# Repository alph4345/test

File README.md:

# Supercapacitor-powered gadgets

Small games, e-ink displays, blinky jewellery and music toys that charge from
USB-C in minutes and run from a **supercapacitor instead of a LiPo**. The
idea comes from the
[rechargeable supercapacitor Fibonacci earrings](https://lectronz.com/products/rechargeable-supercapacitor-fibonacci-earrings-2).

This repository has:

* **[TrinketCore](hardware/trinketcore)**: an all-in-one 40 × 60 mm trinket
  board with PCBWay order files. It has:
  * pads for two capacitors lying flat on the back;
  * USB-C charging with red "charging" and green "full" LEDs;
  * an RP2040 with 16 MB of flash;
  * a socket for OLED or colour TFT modules (the board reads its charge
    level and can show it);
  * a speaker amplifier, buttons, a wake-up clock and an expansion header.
* **[CapCore](hardware/capcore)**: an open, ready-to-order 21 × 48 mm power
  module (KiCad 7). It has a USB-C charger, capacitor protection, a power
  button, a wake-up clock and a 3.3 V output for your microcontroller.
  Gerbers and JLCPCB assembly files are included.
* **[The burst method](docs/trinket-design-method.md)**: how music boxes,
  games, pets and charms last days to weeks on a capacitor, and how colour
  TFT screens fit in.
* **[Energy budget](docs/energy-budget.md)**: how long a capacitor actually
  runs each kind of gadget, plus a [calculator](tools/energy_calc.py).
* **[Choosing a capacitor](docs/choosing-a-capacitor.md)**: lithium-ion
  capacitors vs. ordinary supercapacitors, part numbers, safety rules.
* **[Buy or build?](docs/buy-or-build.md)**: sourcing options and costs.
* **[n0va Books](bookkeeping)**: the bookkeeping app for n0va crafts & creations.
  Customer profiles, branded estimates, invoices and receipts, payments taken
  through Square, sales tax profiles, expenses with receipt photos, a mileage log
  and a tax-time summary. Open `bookkeeping/index.html` in a browser; nothing to install.
* **[Firmware examples](firmware)**: Arduino and MicroPython code for power
  button, sleep/wake, capacitor gauge and shutdown on CapCore, and
  CircuitPython charge-gauge, music-box and e-ink tarot-oracle examples for TrinketCore.

| TrinketCore top | TrinketCore back | CapCore top | CapCore bottom |
|---|---|---|---|
|  |  |  |  |

## The short answer

* **Capacitors are safe and fast but small.** A 3.8 V lithium-ion capacitor
  (LIC) the size of your fingertip stores ~30 mWh, about a tenth of a
  tiny 100 mAh LiPo. The largest common one (16 × 25 mm) stores ~210 mWh. In
  exchange it charges in minutes, lasts tens of thousands of cycles, and is
  far less of a fire risk. Plain 2.7 V supercapacitors (EDLCs) are essentially
  inert but hold about a tenth as much again for the same size.
* **What that runs, per charge** (with a 120 F LIC, 12.5 × 25 mm):
  LED jewellery ~1.5 days · e-ink display updated hourly ~6 weeks ·
  OLED handheld game ~50 min · MP3 player on a speaker ~15 min.
  E-ink and jewellery are great fits, games work for short sessions, music
  players are a stretch. [Details](docs/energy-budget.md).
* **The electronics matter.** LICs must never go below 2.2 V or above 3.8 V,
  and LiPo chargers (4.2 V) would destroy them. CapCore handles that: it
  charges to 3.71 V, disconnects at 2.61 V and stays off until USB returns.
  Build it for ordinary supercapacitors instead by changing two resistors.

## Quick start

1. Pick a capacitor: [choosing a capacitor](docs/choosing-a-capacitor.md).
2. **For a complete trinket:** order TrinketCore assembled from PCBWay with the
   files in [`hardware/trinketcore/fab`](hardware/trinketcore/fab). See
   [ordering](hardware/trinketcore/README.md#ordering-from-pcbway). Plug in a
   display module, fit the capacitors, and load the
   [CircuitPython examples](firmware/trinketcore).
3. **For your own microcontroller board:** order CapCore from JLCPCB with the
   files in [`hardware/capcore/fab`](hardware/capcore/fab) (see
   [ordering](hardware/capcore/README.md#ordering-from-jlcpcb)), run the
   [bring-up checks](hardware/capcore/README.md#bring-up), and wire it to your
   microcontroller ([Pico, Feather, bare chips](hardware/capcore/README.md#connecting-a-microcontroller)).

## Status

Both designs are complete and machine-checked: each schematic and PCB matches
its netlist pin for pin, and KiCad DRC is clean apart from cosmetic footprint
warnings. **Neither board has been manufactured and tested yet.** Order a
small first batch and follow the bring-up steps before building anything you
depend on.

## Repository layout

```
bookkeeping/            n0va Books: customers, invoices, payments, expenses, taxes
docs/                   guides and board renders
firmware/               Arduino + MicroPython (CapCore), CircuitPython (TrinketCore)
hardware/trinketcore/   all-in-one board: KiCad project, PCBWay files, generator scripts
hardware/capcore/       power module: KiCad project, JLCPCB files, generator scripts
tools/energy_calc.py    runtime calculator
```

No license file yet. Pick one before sharing the design: for example
CERN-OHL-P-2.0 for the hardware and MIT for the code.

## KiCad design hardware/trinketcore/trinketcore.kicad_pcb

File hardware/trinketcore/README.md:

# TrinketCore: the all-in-one supercapacitor trinket board

TrinketCore puts everything a small rechargeable gadget needs on one
40 × 60 mm board, ready to order assembled from PCBWay:

* **Room for two capacitors.** They lie flat on the back, wired in parallel.
* **USB-C charging**, with a **red "charging" and a green "full" LED**.
* **A socket for an OLED or colour TFT module.** The microcontroller reads
  the capacitor's charge and can show it on the screen.
* **An RP2040 microcontroller** with 16 MB of flash for code, sounds and
  pictures.
* **A speaker amplifier**, two buttons, a user LED, a wake-up clock and an
  expansion header for LEDs, buttons and a lid switch.

The power side is [CapCore](../capcore)'s proven circuit. It cuts off before
the capacitor over-discharges, uses a soft power switch that turns the whole
board off, and has a buck-boost converter that keeps 3.3 V steady as the
capacitor drains.

| Top | Bottom (capacitor bay) |
|---|---|
|  |  |

*Renders of the actual Gerber layers. The display plugs into the socket along
the top edge. The capacitors solder into the pads on the left and lie flat
inside the outlines on the back.*

## What's on the board

| | |
|---|---|
| Capacitors | BT1 + BT2 in parallel: one or two 3.8 V lithium-ion capacitors (LIC). **EDLC build:** 2.7 V supercapacitors |
| Charging | USB-C, TI BQ25173, 300 mA: two 220 F capacitors fill in about 30 minutes. **Red LED (CHG)** while charging, **green LED (FULL)** when full (USB plugged in) |
| Protection | disconnects at **2.61 V** (LIC) / **1.96 V** (EDLC) and stays off until USB returns; ship mode for storage |
| Power switch | the whole board is **off between uses (about 5 µA)**. It turns on from button A, a lid/tilt switch on `WAKE`, the clock alarm, or USB. Firmware keeps it on with `HOLD` |
| 3.3 V | TI TPS63031 buck-boost, ~500 mA even from a nearly empty capacitor |
| Microcontroller | Raspberry Pi RP2040, 12 MHz crystal, **16 MB** Winbond flash, USB-C data for programming, BOOT and RESET buttons (SWD is not broken out: the USB bootloader is in ROM) |
| Display | **J4**: socket for SPI TFT/OLED modules (GND VCC SCL SDA RES DC CS BLK), backlight dimmable by PWM. **J5**: 4-pin I²C OLED socket. **J8**: Qwiic/STEMMA QT |
| Charge reading | capacitor voltage on an ADC pin, plus "charging" and "USB present" inputs |
| Sound | MAX98357A I²S class-D amplifier, 9 dB gain, shut down when idle; **J7** speaker connector (JST PH 2.0 or solder the wires) |
| Clock | NXP PCF8563 real-time clock: wakes the board on a timer or alarm (virtual pets, e-ink updates) |
| Buttons | **A / POWER** (turns the board on and is readable by firmware), **B**, BOOT, RESET |
| LEDs | red CHG, green FULL (charging), blue user LED on GP25 |
| Expansion | **J6**, 14 pins: GP0–GP7, GP28–GP29 (analog), `WAKE`, `VSYS`, 3V3, GND |
| Board | 4 layers, 40 × 60 × 1.6 mm, all parts on top, PCBWay standard rules (6/6 mil, 0.3 mm holes) |

## Which display?

The socket fits the common 0.96–1.54″ modules, so you can try several and pick
per product. A screen is the second-biggest power draw after a speaker, so
the firmware uses it in short bursts: wake, show, dim, switch off.

| Display | Colour | Draw (with the RP2040 running) | Good for |
|---|---|---|---|
| 0.96″ SSD1306 OLED, 128 × 64 (SPI on J4 or I²C on J5) | mono | ~35–40 mA; dark screens use less | games, menus, pets |
| 1.3–1.54″ ST7789 IPS TFT, 240 × 240 | **full colour** | ~45 mA at 60 % backlight, ~30 mA dimmed | colour animations, charms, games |
| 1.28″ GC9A01 round TFT, 240 × 240 | **full colour** | about the same as the ST7789 | keychain "digital charms" |
| 1.54″ 200 × 200 or 3.7″ 480 × 280 e-paper module (SSD1681 and similar) | black/white, 4 greys, or black/white/red | nothing between refreshes; ~30 mA for 2–3 s per black/white refresh (~14 s for three-colour) | tarot oracles, badges, pets, clocks: always visible |

**Yes, colour TFTs work well.** The backlight is most of the extra power, so
dim it and switch off after a few seconds. On two 220 F capacitors a colour
charm shown for 10 s, 30 times a day, lasts about four weeks. Played
continuously, a colour game lasts about two hours. See
[the design method](../../docs/trinket-design-method.md) for the numbers.

Module pin orders vary. Modules labelled `GND VCC SCL SDA RES DC CS BLK` plug
straight into J4. Seven-pin OLEDs (`GND VCC D0 D1 RES DC CS`) use the first
seven positions. Others, including many GC9A01 modules (`VCC GND ...`), need
short jumper wires. **Check that GND and VCC line up before plugging in.**

**E-ink works too**, and suits anything that should stay visible: the image
costs no power at all once drawn, so the board can switch fully off. E-paper
modules have a BUSY output where TFTs have a backlight input. Wire them to J4
by function (VCC → 3V3, GND, DIN → MOSI, CLK → SCK, CS, DC, RST → RES) with
BUSY on the BLK pin, which the RP2040 reads on GP13. The
[oracle example](../../firmware/trinketcore/circuitpython/oracle/code.py) shows a
random tarot card this way.

## Runtime per charge

LIC build, 85 % converter efficiency, 5 µA standby
([`tools/energy_calc.py`](../../tools/energy_calc.py)):

| Trinket | 1 × 120 F | 1 × 220 F | 2 × 220 F |
|---|---|---|---|
| Music box: 20 s tune + LEDs (~70 mA), 10 plays a day | 75 plays (8 days) | 138 plays (14 days) | 276 plays (4 weeks) |
| Colour TFT charm: 10 s shows (45 mA), 30 a day | 8 days | 14 days | 4 weeks |
| Virtual pet on e-paper: wakes every 30 min (30 mA × 3 s) | 3 weeks | 6 weeks | 3 months* |
| Tarot oracle on e-paper: a card per press (30 mA × 5 s), 10 a day | 600 draws (2 months) | 1,100 draws* | 2,200 draws* |
| OLED game, continuous (40 mA) | 45 min | 80 min | 2.7 h |
| Colour TFT game, continuous (55 mA) | 33 min | 60 min | 2 h |

\* Beyond a month or two the capacitors' own self-discharge dominates.

## Fitting the capacitors

The two capacitor positions sit along the left edge. **Square pad = +.** Each
position takes a 5.0 mm lead pitch (10–12.5 mm cans) or 3.5 mm (8 mm cans).
Bend 16 mm cans' 7.5 mm leads in slightly. Bend the leads 90° so each can lies
flat on the back inside its outline (`CAP 1`, `CAP 2`), with its leads at the
left edge. Stick a strip of Kapton tape under each can, and glue or strap
large cans.

* One capacitor is fine: fit either position.
* Two capacitors must be **the same type** (both LIC, or both EDLC on an EDLC
  build). Sizes may differ.
* Good choices: Eaton HS1225-3R8127-R (120 F, 12.5 × 25 mm) or HS1625-3R8227-R
  (220 F, 16 × 25 mm). See [choosing a capacitor](../../docs/choosing-a-capacitor.md).

> **Never fit a 2.7 V supercapacitor to a board built with the LIC values.**
> It would be charged to 3.71 V and can vent. Tick the build box on the back,
> and measure the charge voltage before fitting capacitors (see
> [Bring-up](#bring-up)).

## Pinout

**J4 display socket** (top edge, pin 1 = square pad, left):
GND · 3V3 · SCK (GP10) · MOSI (GP11) · RES (GP12) · DC (GP9) · CS (GP8) · BLK (GP13 via 100 Ω)

**J5 I²C OLED socket**: GND · 3V3 · SCL (GP17) · SDA (GP16).
**J8 Qwiic**: GND · 3V3 · SDA · SCL. The same bus as the clock (address 0x51),
with 4.7 kΩ pull-ups.

**J6 expansion** (right edge, pin 1 at the top): GP7 · GP6 · GP5 · GP4 · GP3 ·
GP2 · GP1 · GP0 · GP29 · GP28 · WAKE · VSYS · 3V3 · GND. The order matches the
RP2040's pins, which keeps the tracks from crossing; the back silkscreen labels
every pin.

* `WAKE`: pull to GND to switch the board on (lid, tilt, reed or vibration
  switch). For a **lid** that may stay open, put a 1 µF capacitor in series
  with the switch and a 22 MΩ resistor across that capacitor. Opening the
  lid then sends one wake pulse, and the board can still switch itself off.
* `VSYS`: the capacitor voltage (2.6–3.7 V), on only while the board runs.
  Use it for vibration motors or LED strips that tolerate it.
* GPIO pins drive LEDs directly, up to ~8 mA each through a resistor.

**J7 speaker**: 8 Ω, 0.5–1 W. **GPIO map**: see the
[firmware README](../../firmware/trinketcore/README.md#pin-map).

## LEDs and power states

| LED | Meaning |
|---|---|
| red **CHG** | charging |
| green **FULL** | USB plugged in and the capacitors are full |
| red and green blinking alternately | charger fault (for example a capacitor wired backwards, or overheating) |
| blue | yours (GP25) |

With USB plugged in the board also switches on, so a gauge can show charging
progress. Cut jumper **JP1** on the back if plugging in should only charge.
Bridge **JP2** for gadgets without a power button (always on above the
cut-off).

| State | Drain from the capacitors | Leaves the state when… |
|---|---|---|
| Running | your load ÷ ~85 % | firmware drops `HOLD` |
| Off | ~5 µA (clock running) | button A, `WAKE`, clock alarm/timer, USB |
| Cut-off / ship mode | leakage only | USB is plugged in |

## Ordering from PCBWay

Everything is in [`fab/`](fab):

| File | Upload / use |
|---|---|
| `trinketcore-gerbers.zip` | the PCB (Gerbers + drill) |
| `pcbway-bom-lic.csv` (or `-edlc.csv`) | assembly BOM for your build |
| `pcbway-centroid.csv` | pick-and-place positions (mm, origin at the bottom-left corner, same as the Gerbers) |
| `trinketcore-assembly-top.pdf`, `-back.pdf` | assembly drawings, if PCBWay asks |
| `parts-list.csv` | every part, including the ones you fit yourself |

1. On pcbway.com choose **PCB Instant Quote → Quick-order PCB** and upload
   `trinketcore-gerbers.zip`. It should read **40 × 60 mm** and **4 layers**.
2. Board settings:
   * Material FR-4, thickness **1.6 mm**, any solder mask colour.
   * Min track/spacing **6/6 mil**, min hole size **0.3 mm**.
   * Surface finish: **ENIG is recommended** because the RP2040 has 0.4 mm-pitch
     pads. HASL lead-free usually works too.
   * Order number: the back has a `WayWayWay` placeholder where PCBWay can
     print it. Tell them in the notes, or pick the remove-order-number option.
3. Tick **Assembly service**: turnkey, **top side only**, about
   **102 SMD parts (44 unique lines)**, no through-hole parts. Upload
   `pcbway-bom-lic.csv` and `pcbway-centroid.csv`.
4. Paste this note:
   *"BT1, BT2, J4–J7, JP1–JP2: do not populate (customer fits
   capacitors and connectors). J8 and all other parts: assemble as per BOM.
   Please confirm pin 1 of U2, U3, U4, U5, U6, U7, U8 and the LED polarity
   against the silkscreen before assembly."*
5. PCBWay's engineers review the files, source the parts, and email if a part
   needs a substitute. Resistors and capacitors may be any brand with the same
   value, size and tolerance. Approve their placement confirmation photos.

**Rough cost** (prices change, so trust the quote): about US$25–50 for five
4-layer boards, plus assembly (setup ~US$30–50, parts ~US$8–12 per board
with the RP2040, flash and amplifier). Five assembled boards typically land
around US$100–180 before shipping. Most of that is fixed, so ten cost little
more.

The same files work at other assembly houses (the BOM has manufacturer part
numbers, and LCSC numbers where known).

## Bring-up

Before fitting the capacitors:

1. Plug in USB-C. The red and green LEDs may flicker (nothing to charge yet),
   and the board switches on.
2. Measure between the square BT1 pad and GND: about **3.7 V** is the LIC build,
   **2.6 V** the EDLC build.
3. The computer should show an `RPI-RP2` drive (blank flash starts the
   bootloader). Install CircuitPython and try the
   [charge gauge](../../firmware/trinketcore) with a display on J4.

Then unplug USB, fit the capacitors (**square pad = +**), and plug USB back
in: red while charging, green when full. Unplug and press A: the board runs
for about 5 s, or longer if firmware raises `HOLD`. A new capacitor that
arrives below the cut-off keeps the board off until it has charged past it.

## Design files

| File | |
|---|---|
| `trinketcore.kicad_pro/.kicad_sch/.kicad_pcb` | KiCad 7 project |
| `trinketcore-schematic.pdf` | schematic |
| `TrinketCore.kicad_sym`, `TrinketCore.pretty/` | project symbols and footprints |
| `trinketcore.ses` | autorouter result that `route_pcb.py` rebuilds the board from |
| `scripts/` | the generators |

As with CapCore, the board is generated from code:

```
cd hardware/trinketcore/scripts
python3 gen_footprints.py
python3 gen_schematic.py && python3 check_netlist.py
python3 check_place.py
FREEROUTING_JAR=/path/to/freerouting-1.9.0.jar python3 route_pcb.py --autoroute
python3 check_netlist.py --pcb && python3 export_fab.py && python3 render.py
```

`netlist.py` is the single source of truth: parts, values, manufacturer part
numbers and every connection. Autorouting needs Java and
[Freerouting](https://github.com/freerouting/freerouting) 1.9.0 (under
`xvfb-run` on a headless machine); without `--autoroute` the board is rebuilt
from the committed `trinketcore.ses`. The crystal and the power fan-outs are
drawn by hand in `preroute.py`, and a small grid router (`maze.py`) finishes
whatever Freerouting leaves open.

**Verification status:** the schematic and PCB are checked pin-for-pin against
`netlist.py` (378 pins). KiCad DRC with PCBWay's limits reports no errors and
no unconnected items, only one warning: the USB-C footprint differs from the
library copy because its silkscreen was trimmed at the board edge. The routing
is automatic, so some tracks take detours a hand layout wouldn't. The board
has **not been built and tested yet**: treat the first order as a prototype run
and follow the bring-up steps.

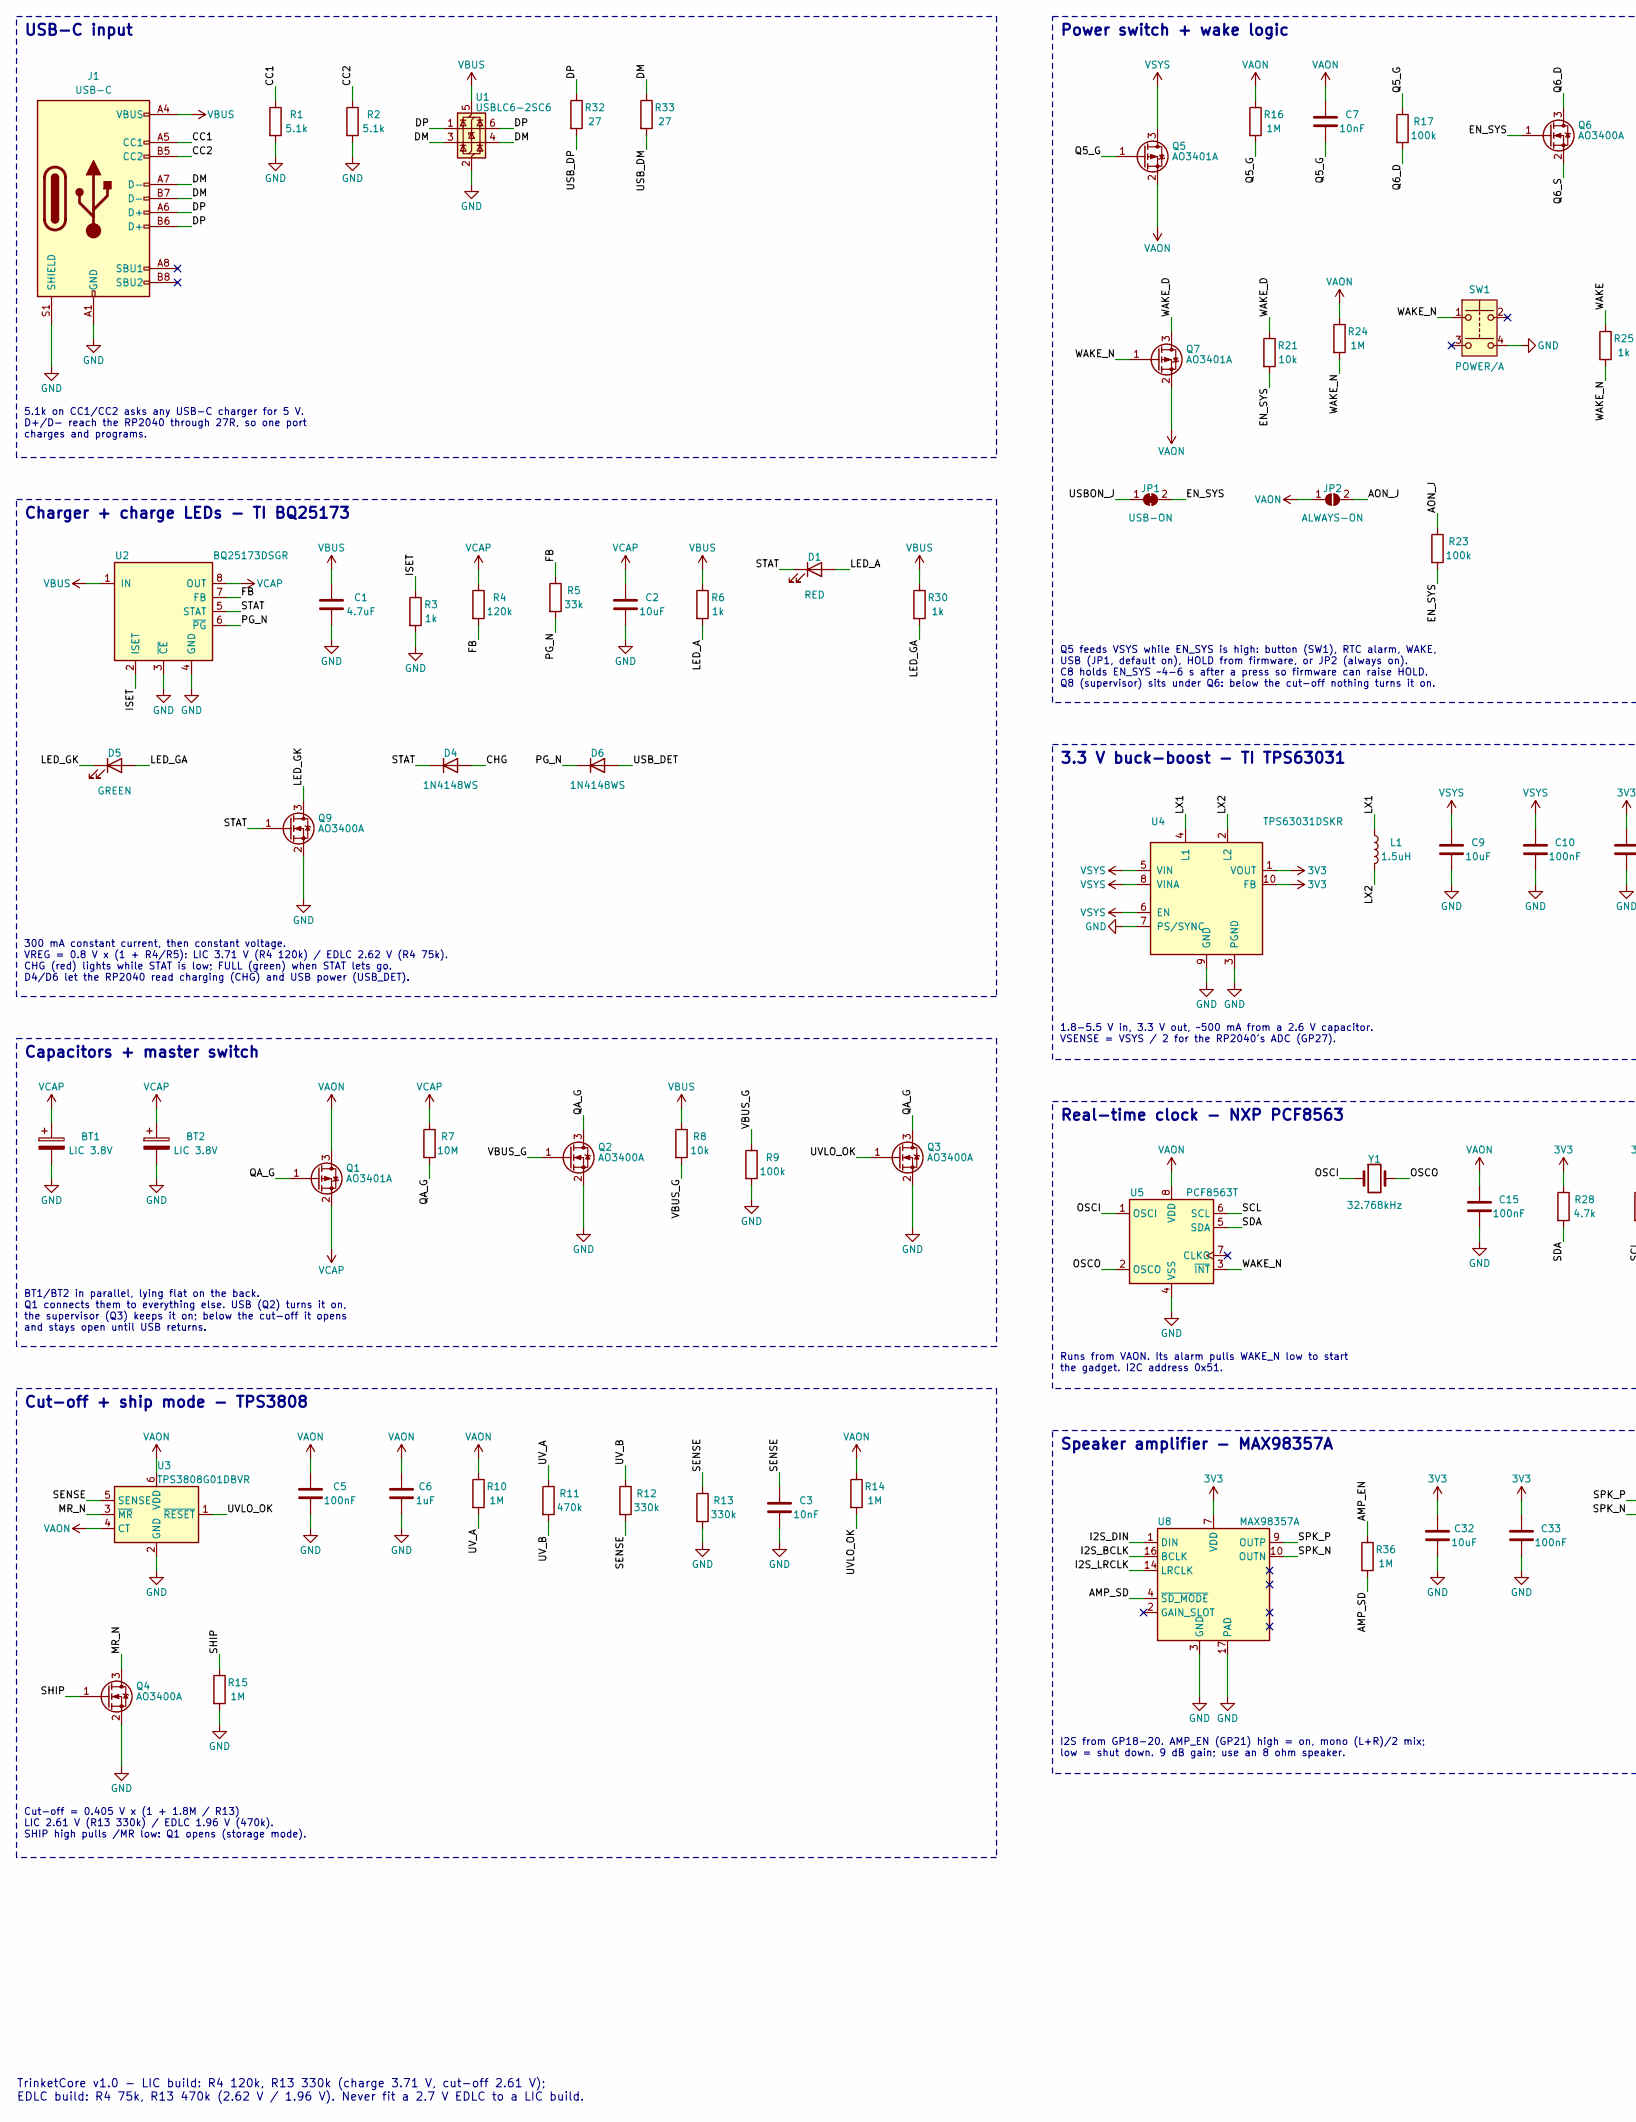
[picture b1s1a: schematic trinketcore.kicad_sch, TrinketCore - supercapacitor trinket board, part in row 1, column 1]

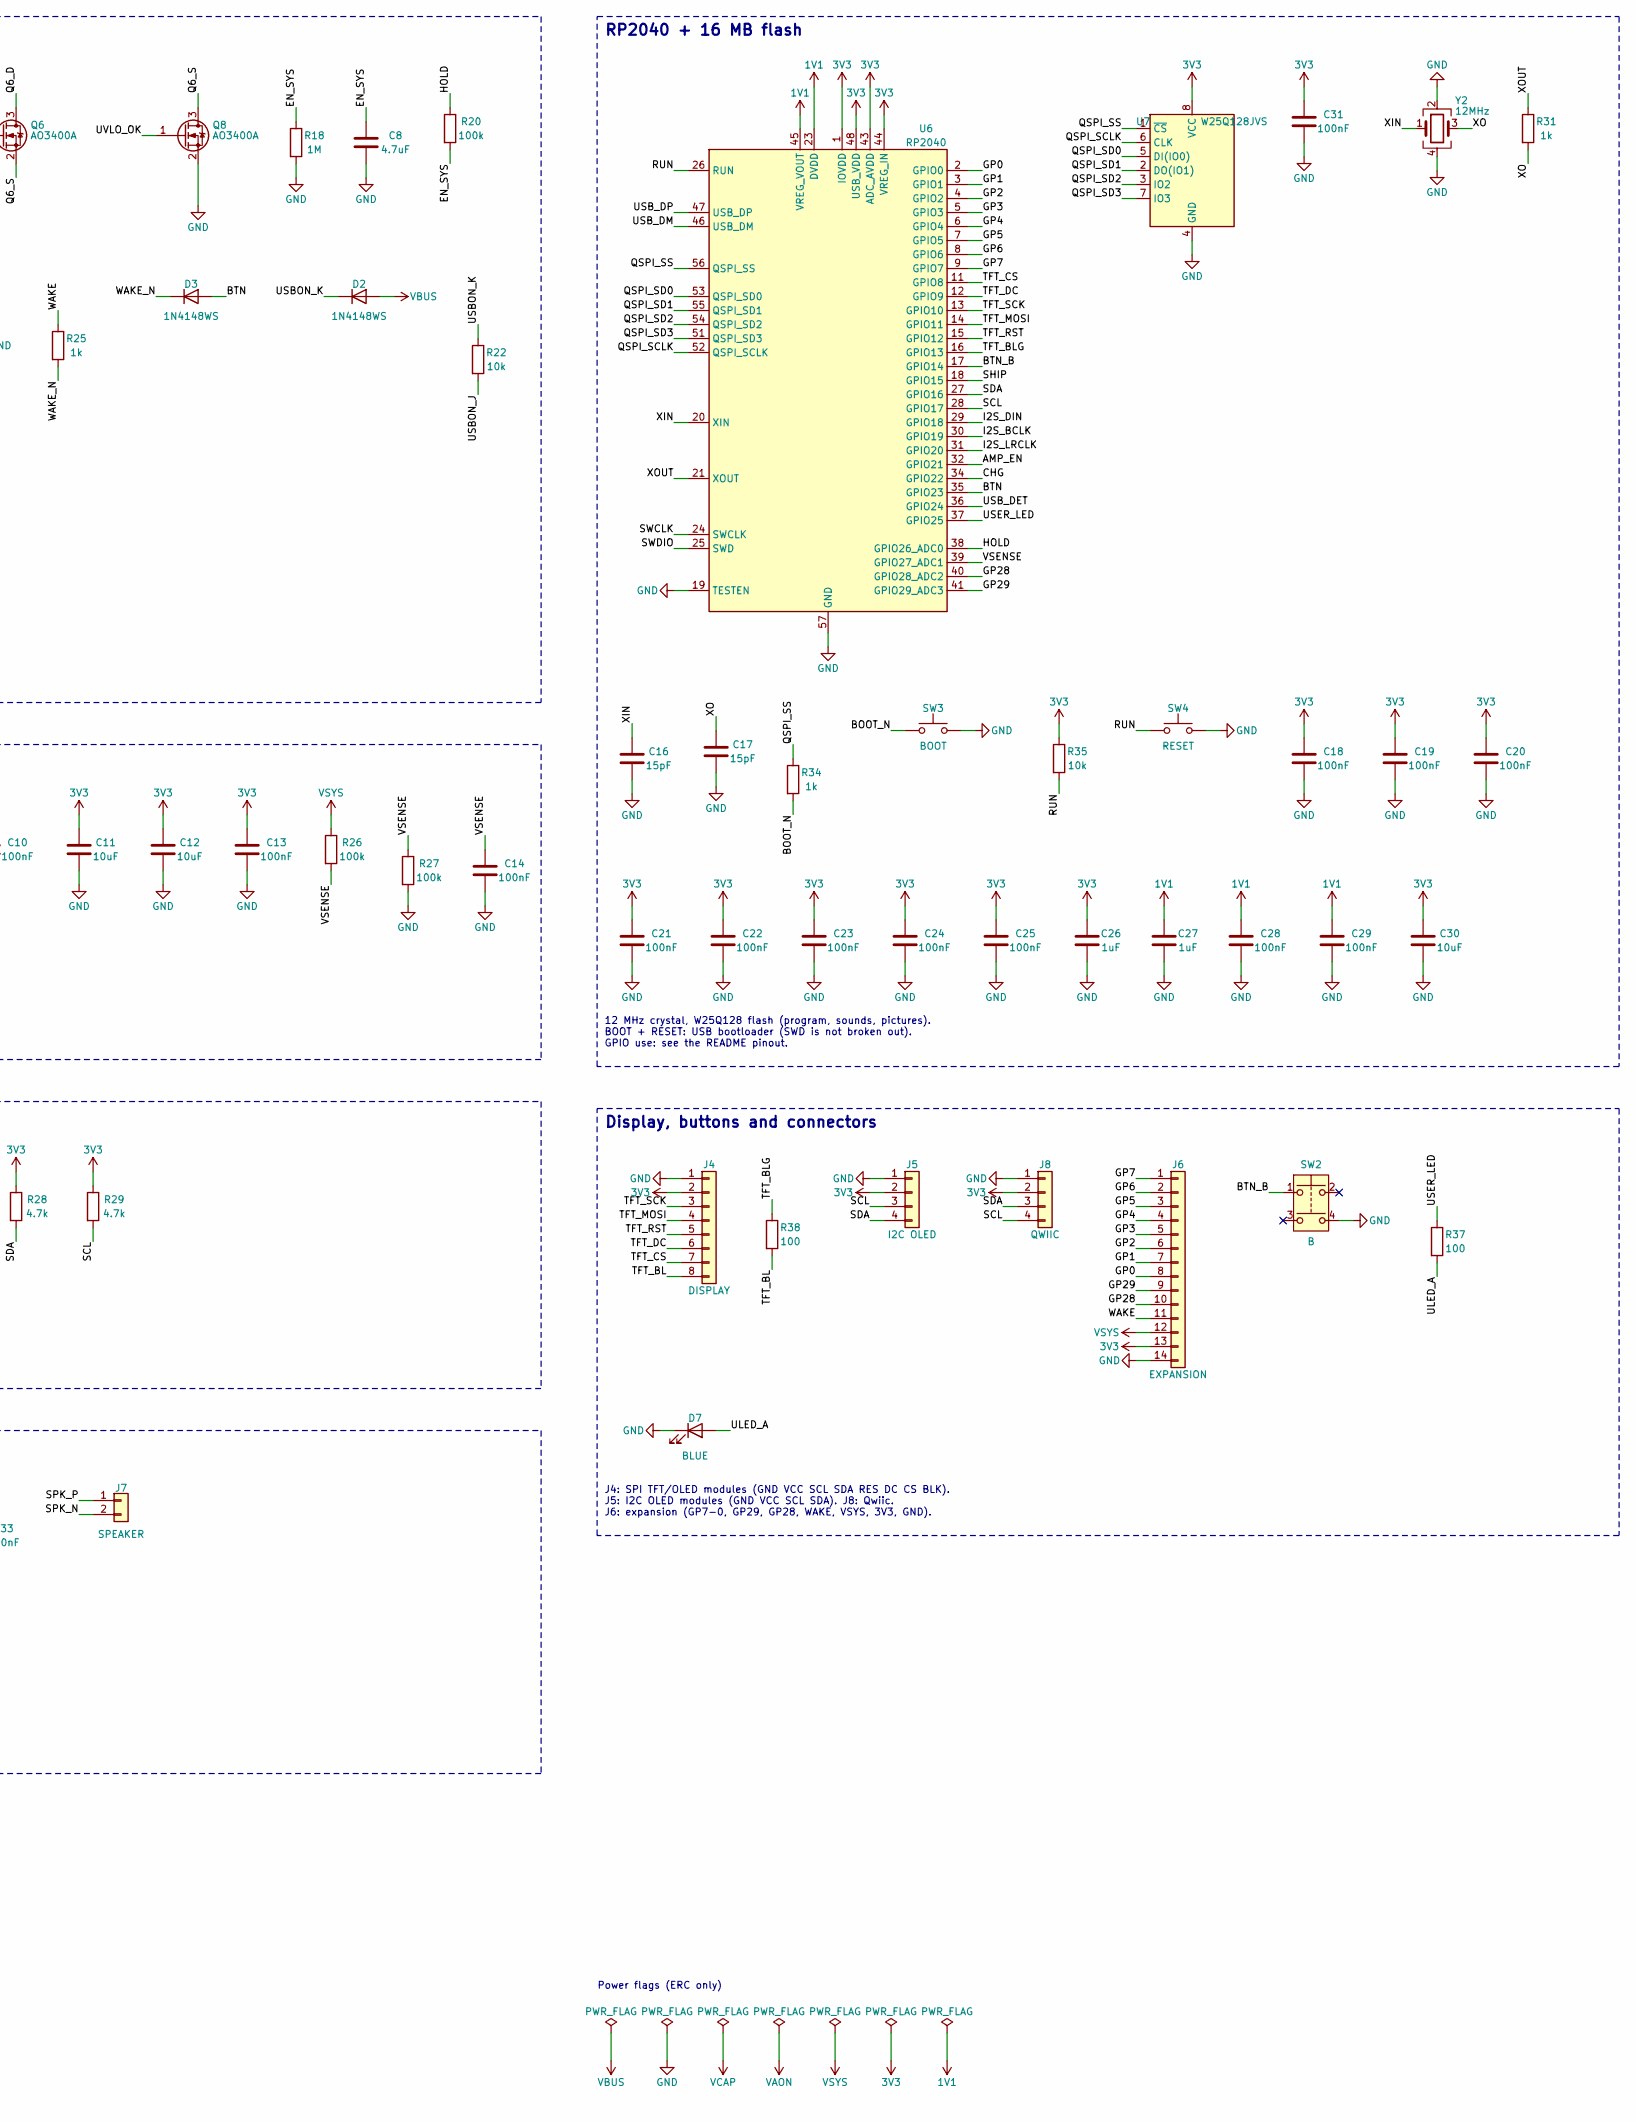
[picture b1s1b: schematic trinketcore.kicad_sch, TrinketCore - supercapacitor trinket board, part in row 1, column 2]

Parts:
BT1, BT2: LIC 3.8V; Supercap_Pads
C1: 4.7uF; C_0805_2012Metric; MPN CL21A475KAQNNNE
C2: 10uF; C_0603_1608Metric; MPN CL10A106KP8NNNC
C3, C7: 10nF; C_0402_1005Metric; MPN CL05B103KB5NNNC
C5, C10, C13, C14, C15, C18, C19, C20, C21, C22, C23, C24, C25, C28, C29, C31, C33: 100nF; C_0402_1005Metric; MPN CL05B104KO5NNNC
C6, C26, C27: 1uF; C_0402_1005Metric; MPN CL05A105KA5NQNC
C8: 4.7uF; C_0603_1608Metric; MPN CL10A475KO8NNNC
C9, C11, C12, C30, C32: 10uF; C_0805_2012Metric; MPN CL21A106KAYNNNE
C16, C17: 15pF; C_0402_1005Metric; MPN CL05C150JB5NNNC
D1: RED; LED_0603_1608Metric; MPN LTST-C191KRKT
D2, D3, D4, D6: 1N4148WS; D_SOD-323; MPN 1N4148WS-7-F
D5: GREEN; LED_0603_1608Metric; MPN LTST-C191KGKT
D7: BLUE; LED_0603_1608Metric; MPN LTST-C191TBKT
J1: USB-C; USB_C_Receptacle_HRO_TYPE-C-31-M-12; MPN TYPE-C-31-M-12
J4: DISPLAY; PinSocket_1x08_P2.54mm_Vertical
J5: I2C OLED; PinSocket_1x04_P2.54mm_Vertical
J6: EXPANSION; PinHeader_1x14_P2.54mm_Vertical
J7: SPEAKER; JST_PH_B2B-PH-K_1x02_P2.00mm_Vertical; MPN B2B-PH-K-S(LF)(SN)
J8: QWIIC; JST_SH_SM04B-SRSS-TB_1x04-1MP_P1.00mm_Horizontal; MPN SM04B-SRSS-TB(LF)(SN)
JP1: USB-ON; SolderJumper-2_P1.3mm_Bridged_RoundedPad1.0x1.5mm
JP2: ALWAYS-ON; SolderJumper-2_P1.3mm_Open_RoundedPad1.0x1.5mm
L1: 1.5uH; L_3015_Universal; MPN NR3015T1R5N
Q1, Q5, Q7: AO3401A; SOT-23; MPN AO3401A
Q2, Q3, Q4, Q6, Q8, Q9: AO3400A; SOT-23; MPN AO3400A
R1, R2: 5.1k; R_0402_1005Metric; MPN RC0402FR-075K1L
R3, R6, R25, R30, R31, R34: 1k; R_0402_1005Metric; MPN RC0402FR-071KL
R4: 120k; R_0402_1005Metric; MPN RC0402FR-07120KL
R5: 33k; R_0402_1005Metric; MPN RC0402FR-0733KL
R7: 10M; R_0402_1005Metric; MPN RC0402FR-0710ML
R8, R21, R22, R35: 10k; R_0402_1005Metric; MPN RC0402FR-0710KL
R9, R17, R20, R23, R26, R27: 100k; R_0402_1005Metric; MPN RC0402FR-07100KL
R10, R14, R15, R16, R18, R24, R36: 1M; R_0402_1005Metric; MPN RC0402FR-071ML
R11: 470k; R_0402_1005Metric; MPN RC0402FR-07470KL
R12, R13: 330k; R_0402_1005Metric; MPN RC0402FR-07330KL
R28, R29: 4.7k; R_0402_1005Metric; MPN RC0402FR-074K7L
R32, R33: 27; R_0402_1005Metric; MPN RC0402FR-0727RL
R37, R38: 100; R_0402_1005Metric; MPN RC0402FR-07100RL
SW1: POWER/A; SW_TS-1187A_5.1x5.1mm; MPN TS-1187A-B-A-B
SW2: B; SW_TS-1187A_5.1x5.1mm; MPN TS-1187A-B-A-B
SW3: BOOT; SW_SPST_B3U-1000P; MPN B3U-1000P
SW4: RESET; SW_SPST_B3U-1000P; MPN B3U-1000P
U1: USBLC6-2SC6; SOT-23-6; MPN USBLC6-2SC6
U2: BQ25173DSGR; WSON-8-1EP_2x2mm_P0.5mm_EP0.9x1.6mm_Vias0.3; MPN BQ25173DSGR
U3: TPS3808G01DBVR; SOT-23-6; MPN TPS3808G01DBVR
U4: TPS63031DSKR; WSON-10-1EP_2.5x2.5mm_P0.5mm_EP1.2x2mm_Vias0.3; MPN TPS63031DSKR
U5: PCF8563T; SOIC-8_3.9x4.9mm_P1.27mm; MPN PCF8563T/5,518
U6: RP2040; QFN-56-1EP_7x7mm_P0.4mm_EP3.2x3.2mm_Vias0.3; MPN RP2040
U7: W25Q128JVS; SOIC-8_5.23x5.23mm_P1.27mm; MPN W25Q128JVSIQ
U8: MAX98357A; TQFN-16-1EP_3x3mm_P0.5mm_EP1.23x1.23mm_Vias0.3; MPN MAX98357AETE+T
Y1: 32.768kHz; Crystal_SMD_3215-2Pin_3.2x1.5mm; MPN Q13FC1350000400
Y2: 12MHz; Crystal_SMD_3225-4Pin_3.2x2.5mm; MPN ABM8-272-T3

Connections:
1V1: C27.1, C28.1, C29.1, U6.23 (DVDD), U6.45 (VREG_VOUT), U6.50 (DVDD)
3V3: C11.1, C12.1, C13.1, C18.1, C19.1, C20.1, C21.1, C22.1, C23.1, C24.1, C25.1, C26.1, C30.1, C31.1, C32.1, C33.1, J4.2, J5.2, J6.13, J8.2, R28.1, R29.1, R35.1, U4.1 (VOUT), U4.10 (FB), U6.1 (IOVDD), U6.10 (IOVDD), U6.22 (IOVDD), U6.33 (IOVDD), U6.42 (IOVDD), U6.43 (ADC_AVDD), U6.44 (VREG_IN), U6.48 (USB_VDD), U6.49 (IOVDD), U7.8 (VCC), U8.7 (VDD), U8.8 (VDD)
AMP_EN: R36.1, U6.32 (GPIO21)
AMP_SD: R36.2, U8.4 (~SD_MODE)
AON_J: JP2.2 (B), R23.1
BOOT_N: R34.2, SW3.1
BTN: D3.2 (A), U6.35 (GPIO23)
BTN_B: SW2.1, U6.17 (GPIO14)
CC1: J1.A5 (CC1), R1.1
CC2: J1.B5 (CC2), R2.1
CHG: D4.2 (A), U6.34 (GPIO22)
DM: J1.A7 (D-), J1.B7 (D-), R33.1, U1.3 (I/O2), U1.4 (I/O2)
DP: J1.A6 (D+), J1.B6 (D+), R32.1, U1.1 (I/O1), U1.6 (I/O1)
EN_SYS: C8.1, JP1.2 (B), Q6.1 (G), R18.1, R20.2, R21.2, R23.2
FB: R4.2, R5.1, U2.7 (FB)
GND: BT1.2, BT2.2, C1.2, C2.2, C3.2, C5.2, C6.2, C8.2, C9.2, C10.2, C11.2, C12.2, C13.2, C14.2, C15.2, C16.2, C17.2, C18.2, C19.2, C20.2, C21.2, C22.2, C23.2, C24.2, C25.2, C26.2, C27.2, C28.2, C29.2, C30.2, C31.2, C32.2, C33.2, D7.1 (K), J1.A1 (GND), J1.A12 (GND), J1.B1 (GND), J1.B12 (GND), J1.S1 (SHIELD), J4.1, J5.1, J6.14, J8.1, Q2.2 (S), Q3.2 (S), Q4.2 (S), Q8.2 (S), Q9.2 (S), R1.2, R2.2, R3.2, R9.2, R13.2, R15.2, R18.2, R27.2, SW1.4, SW2.4, SW3.2, SW4.2, U1.2 (GND), U2.3 (~CE), U2.4 (GND), U2.9 (EP), U3.2 (GND), U4.3 (PGND), U4.7 (PS/SYNC), U4.9 (GND), U4.11 (EP), U5.4 (VSS), U6.19 (TESTEN), U6.57 (GND), U7.4 (GND), U8.3 (GND), U8.11 (GND), U8.15 (GND), U8.17 (PAD), Y2.2, Y2.4
GP0: J6.8, U6.2 (GPIO0)
GP1: J6.7, U6.3 (GPIO1)
GP2: J6.6, U6.4 (GPIO2)
GP3: J6.5, U6.5 (GPIO3)
GP4: J6.4, U6.6 (GPIO4)
GP5: J6.3, U6.7 (GPIO5)
GP6: J6.2, U6.8 (GPIO6)
GP7: J6.1, U6.9 (GPIO7)
GP28: J6.10, U6.40 (GPIO28_ADC2)
GP29: J6.9, U6.41 (GPIO29_ADC3)
HOLD: R20.1, U6.38 (GPIO26_ADC0)
I2S_BCLK: U6.30 (GPIO19), U8.16 (BCLK)
I2S_DIN: U6.29 (GPIO18), U8.1 (DIN)
I2S_LRCLK: U6.31 (GPIO20), U8.14 (LRCLK)
ISET: R3.1, U2.2 (ISET)
LED_A: D1.2 (A), R6.2
LED_GA: D5.2 (A), R30.2
LED_GK: D5.1 (K), Q9.3 (D)
LX1: L1.1, U4.4 (L1)
LX2: L1.2, U4.2 (L2)
MR_N: Q4.3 (D), U3.3 (~MR)
OSCI: U5.1 (OSCI), Y1.1
OSCO: U5.2 (OSCO), Y1.2
PG_N: D6.1 (K), R5.2, U2.6 (~PG)
Q5_G: C7.2, Q5.1 (G), R16.2, R17.1
Q6_D: Q6.3 (D), R17.2
Q6_S: Q6.2 (S), Q8.3 (D)
QA_G: Q1.1 (G), Q2.3 (D), Q3.3 (D), R7.2
QSPI_SCLK: U6.52 (QSPI_SCLK), U7.6 (CLK)
QSPI_SD0: U6.53 (QSPI_SD0), U7.5 (DI(IO0))
QSPI_SD1: U6.55 (QSPI_SD1), U7.2 (DO(IO1))
QSPI_SD2: U6.54 (QSPI_SD2), U7.3 (IO2)
QSPI_SD3: U6.51 (QSPI_SD3), U7.7 (IO3)
QSPI_SS: R34.1, U6.56 (QSPI_SS), U7.1 (~CS)
RUN: R35.2, SW4.1, U6.26 (RUN)
SCL: J5.3, J8.4, R29.2, U5.6 (SCL), U6.28 (GPIO17)
SDA: J5.4, J8.3, R28.2, U5.5 (SDA), U6.27 (GPIO16)
SENSE: C3.1, R12.2, R13.1, U3.5 (SENSE)
SHIP: Q4.1 (G), R15.1, U6.18 (GPIO15)
SPK_N: J7.2, U8.10 (OUTN)
SPK_P: J7.1, U8.9 (OUTP)
STAT: D1.1 (K), D4.1 (K), Q9.1 (G), U2.5 (STAT)
SWCLK: U6.24 (SWCLK)
SWDIO: U6.25 (SWD)
TFT_BL: J4.8, R38.2
TFT_BLG: R38.1, U6.16 (GPIO13)
TFT_CS: J4.7, U6.11 (GPIO8)
TFT_DC: J4.6, U6.12 (GPIO9)
TFT_MOSI: J4.4, U6.14 (GPIO11)
TFT_RST: J4.5, U6.15 (GPIO12)
TFT_SCK: J4.3, U6.13 (GPIO10)
ULED_A: D7.2 (A), R37.2
USBON_J: JP1.1 (A), R22.2
USBON_K: D2.1 (K), R22.1
USB_DET: D6.2 (A), U6.36 (GPIO24)
USB_DM: R33.2, U6.46 (USB_DM)
USB_DP: R32.2, U6.47 (USB_DP)
USER_LED: R37.1, U6.37 (GPIO25)
UVLO_OK: Q3.1 (G), Q8.1 (G), R14.2, U3.1 (~RESET)
UV_A: R10.2, R11.1
UV_B: R11.2, R12.1
VAON: C5.1, C6.1, C7.1, C15.1, JP2.1 (A), Q1.3 (D), Q5.2 (S), Q7.2 (S), R10.1, R14.1, R16.1, R24.1, U3.4 (CT), U3.6 (VDD), U5.8 (VDD)
VBUS: C1.1, D2.2 (A), J1.A4 (VBUS), J1.A9 (VBUS), J1.B4 (VBUS), J1.B9 (VBUS), R6.1, R8.1, R30.1, U1.5 (VBUS), U2.1 (IN)
VBUS_G: Q2.1 (G), R8.2, R9.1
VCAP: BT1.1, BT2.1, C2.1, Q1.2 (S), R4.1, R7.1, U2.8 (OUT)
VSENSE: C14.1, R26.2, R27.1, U6.39 (GPIO27_ADC1)
VSYS: C9.1, C10.1, J6.12, Q5.3 (D), R26.1, U4.5 (VIN), U4.6 (EN), U4.8 (VINA)
WAKE: J6.11, R25.1
WAKE_D: Q7.3 (D), R21.1
WAKE_N: D3.1 (K), Q7.1 (G), R24.2, R25.2, SW1.1, U5.3 (~INT)
XIN: C16.1, U6.20 (XIN), Y2.1
XO: C17.1, R31.2, Y2.3
XOUT: R31.1, U6.21 (XOUT)

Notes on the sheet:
USB-C input
5.1k on CC1/CC2 asks any USB-C charger for 5 V. D+/D- reach the RP2040 through 27R, so one port charges and programs.
Charger + charge LEDs - TI BQ25173
300 mA constant current, then constant voltage. VREG = 0.8 V x (1 + R4/R5): LIC 3.71 V (R4 120k) / EDLC 2.62 V (R4 75k). CHG (red) lights while STAT is low; FULL (green) when STAT lets go. D4/D6 let the RP2040 read charging (CHG) and USB power (USB_DET).
Capacitors + master switch
BT1/BT2 in parallel, lying flat on the back. Q1 connects them to everything else. USB (Q2) turns it on, the supervisor (Q3) keeps it on; below the cut-off it opens and stays open until USB returns.
Cut-off + ship mode - TPS3808
Cut-off = 0.405 V x (1 + 1.8M / R13) LIC 2.61 V (R13 330k) / EDLC 1.96 V (470k). SHIP high pulls /MR low: Q1 opens (storage mode).
Power switch + wake logic
Q5 feeds VSYS while EN_SYS is high: button (SW1), RTC alarm, WAKE, USB (JP1, default on), HOLD from firmware, or JP2 (always on). C8 holds EN_SYS ~4-6 s after a press so firmware can raise HOLD. Q8 (supervisor) sits under Q6: below the cut-off nothing turns it on.
3.3 V buck-boost - TI TPS63031
1.8-5.5 V in, 3.3 V out, ~500 mA from a 2.6 V capacitor. VSENSE = VSYS / 2 for the RP2040's ADC (GP27).
Real-time clock - NXP PCF8563
Runs from VAON. Its alarm pulls WAKE_N low to start the gadget. I2C address 0x51.
Speaker amplifier - MAX98357A
I2S from GP18-20. AMP_EN (GP21) high = on, mono (L+R)/2 mix; low = shut down. 9 dB gain; use an 8 ohm speaker.
RP2040 + 16 MB flash
12 MHz crystal, W25Q128 flash (program, sounds, pictures). BOOT + RESET: USB bootloader (SWD is not broken out). GPIO use: see the README pinout.
Display, buttons and connectors
J4: SPI TFT/OLED modules (GND VCC SCL SDA RES DC CS BLK). J5: I2C OLED modules (GND VCC SCL SDA). J8: Qwiic. J6: expansion (GP7-0, GP29, GP28, WAKE, VSYS, 3V3, GND).
Power flags (ERC only)
TrinketCore v1.0 - LIC build: R4 120k, R13 330k (charge 3.71 V, cut-off 2.61 V); EDLC build: R4 75k, R13 470k (2.62 V / 1.96 V). Never fit a 2.7 V EDLC to a LIC build.

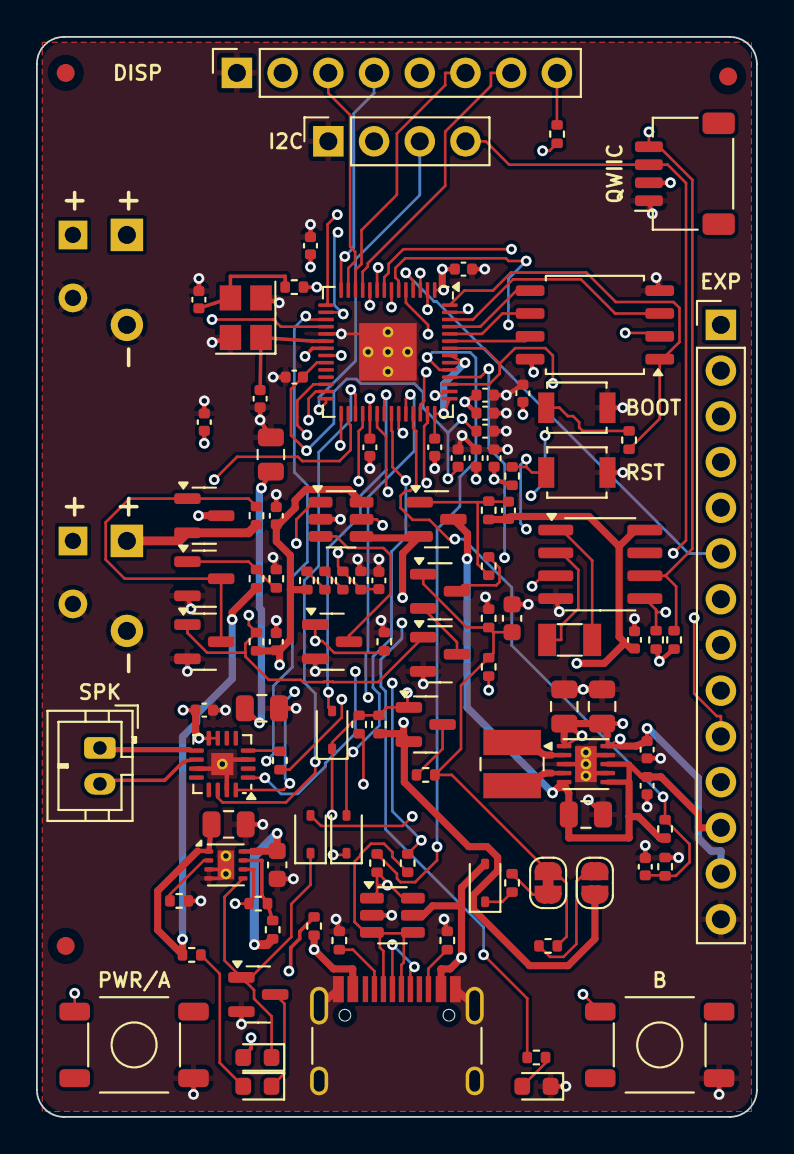
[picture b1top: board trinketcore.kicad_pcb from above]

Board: 4 copper layers, 40.0 x 60.0 mm, 113 parts (0 on the bottom side), 87 nets.

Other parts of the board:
FID1, FID2, FID3: Fiducial; Fiducial_1mm_Mask2mm

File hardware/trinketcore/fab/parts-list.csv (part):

Ref,Value (LIC build),Value (EDLC build),Manufacturer,MPN,Footprint,LCSC,Assembled,Notes
BT1,LIC 3.8V,EDLC 2.7V,,,Supercap_Pads,,no (you fit it),your lithium-ion capacitor; lies flat on the back (not assembled)
BT2,LIC 3.8V,EDLC 2.7V,,,Supercap_Pads,,no (you fit it),your lithium-ion capacitor; lies flat on the back (not assembled)
C1,4.7uF,4.7uF,Samsung Electro-Mechanics,CL21A475KAQNNNE,C_0805_2012Metric,C1779,yes,charger input
C2,10uF,10uF,Samsung Electro-Mechanics,CL10A106KP8NNNC,C_0603_1608Metric,C19702,yes,charger output
C3,10nF,10nF,Samsung Electro-Mechanics,CL05B103KB5NNNC,C_0402_1005Metric,C15195,yes,ignores millisecond dips from load steps
C5,100nF,100nF,Samsung Electro-Mechanics,CL05B104KO5NNNC,C_0402_1005Metric,C1525,yes,U3 supply
C6,1uF,1uF,Samsung Electro-Mechanics,CL05A105KA5NQNC,C_0402_1005Metric,C52923,yes,VAON bulk
C7,10nF,10nF,Samsung Electro-Mechanics,CL05B103KB5NNNC,C_0402_1005Metric,C15195,yes,soft start
C8,4.7uF,4.7uF,Samsung Electro-Mechanics,CL10A475KO8NNNC,C_0603_1608Metric,C19666,yes,keeps power on ~4-6 s after a button press so firmware can raise HOLD
C9,10uF,10uF,Samsung Electro-Mechanics,CL21A106KAYNNNE,C_0805_2012Metric,C15850,yes,regulator input
C10,100nF,100nF,Samsung Electro-Mechanics,CL05B104KO5NNNC,C_0402_1005Metric,C1525,yes,VINA bypass
C11,10uF,10uF,Samsung Electro-Mechanics,CL21A106KAYNNNE,C_0805_2012Metric,C15850,yes,regulator output
C12,10uF,10uF,Samsung Electro-Mechanics,CL21A106KAYNNNE,C_0805_2012Metric,C15850,yes,regulator output
C13,100nF,100nF,Samsung Electro-Mechanics,CL05B104KO5NNNC,C_0402_1005Metric,C1525,yes,output HF bypass
C14,100nF,100nF,Samsung Electro-Mechanics,CL05B104KO5NNNC,C_0402_1005Metric,C1525,yes,ADC sample charge
C15,100nF,100nF,Samsung Electro-Mechanics,CL05B104KO5NNNC,C_0402_1005Metric,C1525,yes,RTC supply
C16,15pF,15pF,Samsung Electro-Mechanics,CL05C150JB5NNNC,C_0402_1005Metric,C1548,yes,crystal load
C17,15pF,15pF,Samsung Electro-Mechanics,CL05C150JB5NNNC,C_0402_1005Metric,C1548,yes,crystal load
C18,100nF,100nF,Samsung Electro-Mechanics,CL05B104KO5NNNC,C_0402_1005Metric,C1525,yes,IOVDD pin 1
C19,100nF,100nF,Samsung Electro-Mechanics,CL05B104KO5NNNC,C_0402_1005Metric,C1525,yes,IOVDD pin 10
C20,100nF,100nF,Samsung Electro-Mechanics,CL05B104KO5NNNC,C_0402_1005Metric,C1525,yes,IOVDD pin 22
C21,100nF,100nF,Samsung Electro-Mechanics,CL05B104KO5NNNC,C_0402_1005Metric,C1525,yes,IOVDD pin 33
C22,100nF,100nF,Samsung Electro-Mechanics,CL05B104KO5NNNC,C_0402_1005Metric,C1525,yes,IOVDD pin 42
C23,100nF,100nF,Samsung Electro-Mechanics,CL05B104KO5NNNC,C_0402_1005Metric,C1525,yes,IOVDD pin 49
C24,100nF,100nF,Samsung Electro-Mechanics,CL05B104KO5NNNC,C_0402_1005Metric,C1525,yes,USB_VDD
C25,100nF,100nF,Samsung Electro-Mechanics,CL05B104KO5NNNC,C_0402_1005Metric,C1525,yes,ADC_AVDD
C26,1uF,1uF,Samsung Electro-Mechanics,CL05A105KA5NQNC,C_0402_1005Metric,C52923,yes,VREG_IN
C27,1uF,1uF,Samsung Electro-Mechanics,CL05A105KA5NQNC,C_0402_1005Metric,C52923,yes,VREG_VOUT
C28,100nF,100nF,Samsung Electro-Mechanics,CL05B104KO5NNNC,C_0402_1005Metric,C1525,yes,DVDD pin 23
C29,100nF,100nF,Samsung Electro-Mechanics,CL05B104KO5NNNC,C_0402_1005Metric,C1525,yes,DVDD pin 50
C30,10uF,10uF,Samsung Electro-Mechanics,CL21A106KAYNNNE,C_0805_2012Metric,C15850,yes,3V3 bulk at the RP2040
C31,100nF,100nF,Samsung Electro-Mechanics,CL05B104KO5NNNC,C_0402_1005Metric,C1525,yes,flash supply
C32,10uF,10uF,Samsung Electro-Mechanics,CL21A106KAYNNNE,C_0805_2012Metric,C15850,yes,amplifier supply
C33,100nF,100nF,Samsung Electro-Mechanics,CL05B104KO5NNNC,C_0402_1005Metric,C1525,yes,amplifier supply
D1,RED,RED,Lite-On,LTST-C191KRKT,LED_0603_1608Metric,,yes,CHG: on while charging
D2,1N4148WS,1N4148WS,Diodes Incorporated,1N4148WS-7-F,D_SOD-323,C2128,yes,USB power turns the gadget on
D3,1N4148WS,1N4148WS,Diodes Incorporated,1N4148WS-7-F,D_SOD-323,C2128,yes,lets the RP2040 read the power button
D4,1N4148WS,1N4148WS,Diodes Incorporated,1N4148WS-7-F,D_SOD-323,C2128,yes,lets the RP2040 read the charge status without back-feeding
D5,GREEN,GREEN,Lite-On,LTST-C191KGKT,LED_0603_1608Metric,,yes,FULL: on when charged (USB plugged in)
D6,1N4148WS,1N4148WS,Diodes Incorporated,1N4148WS-7-F,D_SOD-323,C2128,yes,lets the RP2040 see USB power (reads low when plugged in)
D7,BLUE,BLUE,Lite-On,LTST-C191TBKT,LED_0603_1608Metric,,yes,"user LED (GP25, like a Pico)"
J1,USB-C,USB-C,Korean Hroparts Elec,TYPE-C-31-M-12,USB_C_Receptacle_HRO_TYPE-C-31-M-12,C165948,yes,"USB-C receptacle, USB 2.0, 16 pin"
J4,DISPLAY,DISPLAY,,,PinSocket_1x08_P2.54mm_Vertical,,no (you fit it),SPI TFT/OLED module socket: GND VCC SCL SDA RES DC CS BLK
J5,I2C OLED,I2C OLED,,,PinSocket_1x04_P2.54mm_Vertical,,no (you fit it),I2C OLED module socket: GND VCC SCL SDA
J6,EXPANSION,EXPANSION,,,PinHeader_1x14_P2.54mm_Vertical,,no (you fit it),"expansion header: LEDs, buttons, sensors, lid switch"
J7,SPEAKER,SPEAKER,JST,B2B-PH-K-S(LF)(SN),JST_PH_B2B-PH-K_1x02_P2.00mm_Vertical,,no (you fit it),"speaker, 8 ohm (JST PH 2.0 mm, or solder the wires)"
J8,QWIIC,QWIIC,JST,SM04B-SRSS-TB(LF)(SN),JST_SH_SM04B-SRSS-TB_1x04-1MP_P1.00mm_Horizontal,,yes,Qwiic / STEMMA QT I2C connector
JP1,USB-ON,USB-ON,,,SolderJumper-2_P1.3mm_Bridged_RoundedPad1.0x1.5mm,,no (you fit it),cut to stop USB from turning the gadget on
JP2,ALWAYS-ON,ALWAYS-ON,,,SolderJumper-2_P1.3mm_Open_RoundedPad1.0x1.5mm,,no (you fit it),bridge for always-on (no power button)
L1,1.5uH,1.5uH,Taiyo Yuden,NR3015T1R5N,L_3015_Universal,C7497056,yes,"1.5 uH, 3 x 3 mm shielded, Isat >= 1.5 A"
Q1,AO3401A,AO3401A,Alpha & Omega Semiconductor,AO3401A,SOT-23,C15127,yes,master switch: opens below 2.6 V or in ship mode
Q2,AO3400A,AO3400A,Alpha & Omega Semiconductor,AO3400A,SOT-23,C20917,yes,USB power turns Q1 on (wakes from cut-off)
Q3,AO3400A,AO3400A,Alpha & Omega Semiconductor,AO3400A,SOT-23,C20917,yes,keeps Q1 on while the capacitor is healthy
Q4,AO3400A,AO3400A,Alpha & Omega Semiconductor,AO3400A,SOT-23,C20917,yes,SHIP high forces a cut-off (storage mode)
Q5,AO3401A,AO3401A,Alpha & Omega Semiconductor,AO3401A,SOT-23,C15127,yes,load switch with soft start
Q6,AO3400A,AO3400A,Alpha & Omega Semiconductor,AO3400A,SOT-23,C20917,yes,turns the gadget on
Q7,AO3401A,AO3401A,Alpha & Omega Semiconductor,AO3401A,SOT-23,C15127,yes,button / RTC alarm turns the gadget on
Q8,AO3400A,AO3400A,Alpha & Omega Semiconductor,AO3400A,SOT-23,C20917,yes,"in series with Q6: nothing turns the gadget on below the cut-off, not even USB"
Q9,AO3400A,AO3400A,Alpha & Omega Semiconductor,AO3400A,SOT-23,C20917,yes,lights FULL when the charger releases STAT
R1,5.1k,5.1k,Yageo,RC0402FR-075K1L,R_0402_1005Metric,C25905,yes,CC1 sink pull-down
R2,5.1k,5.1k,Yageo,RC0402FR-075K1L,R_0402_1005Metric,C25905,yes,CC2 sink pull-down
R3,1k,1k,Yageo,RC0402FR-071KL,R_0402_1005Metric,C11702,yes,charge current = 300 V / R3 = 300 mA
R4,120k,75k,Yageo,RC0402FR-07120KL,R_0402_1005Metric,C25750,yes,charge voltage = 0.8 V x (1 + R4/R5) = 3.71 V
R5,33k,33k,Yageo,RC0402FR-0733KL,R_0402_1005Metric,C25779,yes,returned to /PG so the divider cannot drain the capacitor without USB
R6,1k,1k,Yageo,RC0402FR-071KL,R_0402_1005Metric,C11702,yes,charging LED current
R7,10M,10M,Yageo,RC0402FR-0710ML,R_0402_1005Metric,C26082,yes,Q1 off by default
R8,10k,10k,Yageo,RC0402FR-0710KL,R_0402_1005Metric,C25744,yes,
R9,100k,100k,Yageo,RC0402FR-07100KL,R_0402_1005Metric,C25741,yes,
R10,1M,1M,Yageo,RC0402FR-071ML,R_0402_1005Metric,C26083,yes,UVLO divider top (1/3)
R11,470k,470k,Yageo,RC0402FR-07470KL,R_0402_1005Metric,C25790,yes,UVLO divider top (2/3)
R12,330k,330k,Yageo,RC0402FR-07330KL,R_0402_1005Metric,C25778,yes,UVLO divider top (3/3)
R13,330k,470k,Yageo,RC0402FR-07330KL,R_0402_1005Metric,C25778,yes,cut-off = 0.405 V x (1 + 1.8M/R13) = 2.61 V
R14,1M,1M,Yageo,RC0402FR-071ML,R_0402_1005Metric,C26083,yes,RESET pull-up
R15,1M,1M,Yageo,RC0402FR-071ML,R_0402_1005Metric,C26083,yes,SHIP idles low
R16,1M,1M,Yageo,RC0402FR-071ML,R_0402_1005Metric,C26083,yes,Q5 off by default
R17,100k,100k,Yageo,RC0402FR-07100KL,R_0402_1005Metric,C25741,yes,soft start
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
